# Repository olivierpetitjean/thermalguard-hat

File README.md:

# ThermalGuard HAT

ThermalGuard HAT is a Raspberry Pi HAT for monitoring and controlling airflow in a server rack or enclosed equipment bay.

This repository contains both the hardware design and the software stack:

- a custom KiCad HAT
- a Python hardware service running on the Raspberry Pi
- a .NET 8 API
- an Angular web dashboard

## Demo

https://github.com/user-attachments/assets/547ba5f1-9dda-4290-b39c-db074ba426f6

## Board Renders And Wiring

### KiCad 3D render - front

### KiCad 3D render - back

### Wiring overview

## Features

- System monitoring for onboard temperature, power consumption and relative humidity
- Two configurable temperature probes for rack, ambient or custom placement
- Dual fan control with RPM tracking and airflow estimation
- Onboard display showing temperatures, fan RPM, IP address and MAC address
- Automatic fan curves with linked or independent behavior
- Temporary boost mode to force maximum cooling for a defined duration
- Audible alert when a fan or temperature probe is disconnected
- Onboard button control to mute or disable the audible alert
- Web dashboard with live status cards and historical charts
- History browsing by custom period, day or hour
- Local or remote access with authentication
- Kiosk mode for dedicated wall display or rack display usage
- End-to-end installation assistant, including kiosk setup
- Configurable SQLite storage location, including external USB or disk-based storage

The reference platform for this project is a Raspberry Pi 2B. The goal is also to make practical use of older Raspberry Pi hardware for a dedicated monitoring appliance, rather than requiring a newer and more expensive board.

## Repository Structure

```text
thermalguard-hat/
|-- backend/
|   |-- src/      .NET 8 API, persistence, workers, static frontend hosting
|   `-- tests/    .NET test project
|-- frontend/     Angular frontend
|-- services/     Raspberry Pi hardware service and Python tests
|-- kicad/        KiCad project for the HAT PCB
|-- config/       Shared example configuration
|-- docs/         README media assets
`-- install.sh    Raspberry Pi installation script
```

## Hardware

Main hardware blocks currently present in the project:

- Raspberry Pi 2B host
- custom HAT PCB designed in KiCad
- 2 x DS18B20 probes
- 1 x SHT31D temperature and humidity sensor
- 2 x PWM-controlled fans
- fan tachometer and current measurement circuitry
- OLED display and onboard controls

The repository is not only a software project. It also includes the PCB design files required to fabricate the HAT.

## Software Architecture

```mermaid
flowchart TB
    browser([Browser])
    kiosk([Kiosk Display])
    front["Angular Dashboard"]
    api[".NET 8 API"]
    proxy["MQTT Proxy (/mqtt)"]
    mqtt[("Mosquitto Broker")]
    py["Python Hardware Service"]
    db[("SQLite Database")]
    hw["Sensors / Fans / GPIO"]
    svc["systemd"]

    browser -->|"UI"| front
    kiosk -->|"Kiosk UI"| front
    front -->|"REST"| api
    front -->|"WebSocket MQTT"| proxy
    proxy -->|"MQTT"| mqtt
    mqtt -->|"Live telemetry"| proxy
    py -->|"Publish"| mqtt
    py -->|"Store samples"| db
    api -->|"Read / write"| db
    api -->|"Control service"| svc
    svc -->|"Manage"| py
    py -->|"Read / drive"| hw

    classDef client fill:#202534,stroke:#90a4ff,color:#ffffff,stroke-width:1.5px;
    classDef ui fill:#2f3d56,stroke:#6ea8fe,color:#ffffff,stroke-width:1.5px;
    classDef backend fill:#304b46,stroke:#58c4a3,color:#ffffff,stroke-width:1.5px;
    classDef msg fill:#4b3561,stroke:#d08bff,color:#ffffff,stroke-width:1.5px;
    classDef data fill:#5a4330,stroke:#f2a65a,color:#ffffff,stroke-width:1.5px;
    classDef device fill:#4a3f46,stroke:#ff7b7b,color:#ffffff,stroke-width:1.5px;

    class browser,kiosk client;
    class front ui;
    class api,proxy,svc backend;
    class mqtt msg;
    class db data;
    class py,hw device;
```

### Python service

The Python service is the hardware-facing part of the system. It:

- initializes GPIO and sensors
- controls the fans
- reads live measurements
- publishes telemetry on MQTT
- persists data into SQLite

Main entry points:

- [services/main.py](services/main.py)
- [services/service.py](services/service.py)

### Backend API

The backend is a .NET 8 application that:

- serves the web application
- exposes authenticated API endpoints
- stores and queries historical data
- exposes configuration for the frontend
- manages service status operations

Main entry points:

- [backend/src/NetApi/Program.cs](backend/src/NetApi/Program.cs)
- [backend/src/NetApi/Api/Controllers](backend/src/NetApi/Api/Controllers)

### Frontend

The frontend is an Angular application providing:

- dashboard views
- setup and login screens
- kiosk mode
- live MQTT-backed monitoring cards and graphs

Main entry points:

- [frontend/src/app/features/dashboard/pages/dashboard.component.ts](frontend/src/app/features/dashboard/pages/dashboard.component.ts)
- [frontend/src/app/core/app.routes.ts](frontend/src/app/core/app.routes.ts)

## Dashboard

The web interface provides both live monitoring cards and historical charts.

### Live overview

### History view

## Kiosk Mode

ThermalGuard HAT can run in kiosk mode for a dedicated rack display, with optional autologin, Chromium autostart, cursor hiding and screen blanking control.

https://github.com/user-attachments/assets/b98a219e-978e-4593-a772-88bbc4d270f7

## Installation

Run the installation script on the Raspberry Pi as root:

```bash
sudo bash -c "$(curl -sSL https://raw.githubusercontent.com/olivierpetitjean/thermalguard-hat/main/install.sh)"
```

The script installs the software stack, prepares the Raspberry Pi environment and deploys the backend, frontend and Python service.

## Storage Recommendation

For a permanent installation, it is strongly recommended to store the SQLite database on an external storage device such as:

- a USB flash drive
- an external SSD
- an external hard drive

Reason:

- the system performs repeated read and write operations
- keeping the database on the Raspberry Pi SD card increases wear
- the SD card also hosts the operating system, so avoiding unnecessary writes improves reliability

The database location is configurable through the shared connection string in [config/settings.example.json](config/settings.example.json).

## Configuration

The main configuration reference is [config/settings.example.json](config/settings.example.json).

The setup wizard intentionally hides a few advanced low-level values such as the GPIO chip index and PWM channel mapping. They remain available in the shared configuration file if manual tuning is ever needed.

The installation also runs an interactive configuration wizard. Its main sections are:

| Wizard section | What it configures |
|---|---|
| `API & Security` | CORS origin, JWT secret, token lifetime, retention policy and kiosk IP bypass rules |
| `Display & Naming` | Dashboard title, sensor names, fan names, locale, units and airflow display values |
| `Kiosk Mode` | Dedicated kiosk display behavior, local user, inline layout, cursor hiding, autologin, screen blanking and autostart |
| `MQTT Broker` | Local Mosquitto setup, WebSocket port, optional local authentication and optional MQTT bridge settings |
| `1-Wire Temperature Sensors` | Detection and assignment of the two DS18B20 probe identifiers |
| `Thresholds & Timing` | System fan threshold, database write interval, LCD screen standby delay, fan tach filter and PWM timing settings |

If kiosk mode is enabled, the installer then runs a second kiosk-specific step to apply the desktop autologin, screen blanking and Chromium autostart configuration.

### Core settings

| Key | Purpose | Example |
|---|---|---|
| `ConnectionStrings.WebApiDatabase` | Shared SQLite database path used by the API and Python service | `Data Source=/opt/thermalguard-hat/api/db/LocalDatabase.db` |
| `RetentionDays` | Number of days of historical data to keep | `30` |
| `Auth.JwtSecret` | Secret used to sign JWT tokens | `change-me-in-production-at-least-32-chars!!` |
| `Auth.TokenExpiryHours` | JWT validity duration in hours | `12` |
| `AllowedOrigins` | Allowed frontend origin for CORS | `http://raspberrypi.local` |

### MQTT and broker settings

| Key | Purpose | Example |
|---|---|---|
| `BrokerHostSettings.Host` | MQTT broker hostname or IP | `127.0.0.1` |
| `BrokerHostSettings.Port` | MQTT TCP port | `1883` |
| `BrokerHostSettings.WsPort` | MQTT over WebSocket port | `1884` |
| `BrokerHostSettings.User` | MQTT username | `your-user` |
| `BrokerHostSettings.Password` | MQTT password | `your-password` |
| `BrokerHostSettings.UseTls` | Enable TLS for broker communication | `false` |
| `Mosquitto.Local.Authentication.Enabled` | Enable authentication on local Mosquitto | `false` |
| `Mosquitto.Bridge.Enabled` | Enable broker bridge mode | `false` |
| `Mosquitto.Bridge.Host` | Upstream broker hostname | `mqtt.example.com` |
| `Mosquitto.Bridge.Port` | Upstream broker port | `1883` |

### Sensors, cooling and hardware pins

| Key | Purpose | Example |
|---|---|---|
| `Python.Sensor1Uid` | 1-Wire identifier for probe 1 | `xxxxxxxxxxxx` |
| `Python.Sensor2Uid` | 1-Wire identifier for probe 2 | `xxxxxxxxxxxx` |
| `Python.SysFanThreshold` | Temperature threshold for the system fan | `38` |
| `Python.Fan1Pin` | PWM pin for fan 1 | `12` |
| `Python.Fan2Pin` | PWM pin for fan 2 | `13` |
| `Python.Fan1Sensor` | Tachometer input for fan 1 | `25` |
| `Python.Fan2Sensor` | Tachometer input for fan 2 | `24` |
| `Python.SystemFan` | GPIO pin for the auxiliary system fan | `23` |
| `Python.SysBuzzer` | GPIO pin for the buzzer | `22` |
| `Python.Button1Pin` | GPIO pin for button 1 | `17` |
| `Python.Button2Pin` | GPIO pin for button 2 | `0` |

### Display and UI labels

| Key | Purpose | Example |
|---|---|---|
| `Display.DashboardTitle` | Dashboard title shown in the UI | `Dashboard` |
| `Display.Sensor1Name` | Label for probe 1 | `Rack` |
| `Display.Sensor2Name` | Label for probe 2 | `Ambient` |
| `Display.Fan1Name` | Label for fan 1 | `Intake Fan` |
| `Display.Fan2Name` | Label for fan 2 | `Exhaust Fan` |
| `Display.Locale` | UI locale | `en-US` |
| `Display.TemperatureUnit` | Temperature unit | `C` |
| `Display.AirflowUnit` | Airflow unit displayed in the UI | `m3h` |
| `Display.Fan1MaxAirflow` | Reference airflow value for fan 1 | `95.0` |
| `Display.Fan2MaxAirflow` | Reference airflow value for fan 2 | `95.0` |

### Kiosk settings

| Key | Purpose | Example |
|---|---|---|
| `Kiosk.BypassIPs` | IP addresses allowed to access kiosk mode without standard login | `[]` |
| `KioskSetup.Enabled` | Enable kiosk setup during installation | `false` |
| `KioskSetup.User` | Desktop user used for kiosk autologin | `pi` |
| `KioskSetup.HideCursor` | Hide mouse cursor in kiosk mode | `true` |
| `KioskSetup.DesktopAutologin` | Enable desktop autologin | `true` |
| `KioskSetup.DisableScreenBlanking` | Disable screen blanking and sleep | `true` |
| `KioskSetup.Autostart` | Launch kiosk automatically on boot | `true` |

## Security

- API endpoints are protected with JWT authentication except the authentication bootstrap endpoints
- passwords are hashed with BCrypt
- the JWT secret must be changed before deployment
- CORS origins should be restricted to the actual deployed frontend origin

## License

MIT. See [LICENSE](LICENSE).

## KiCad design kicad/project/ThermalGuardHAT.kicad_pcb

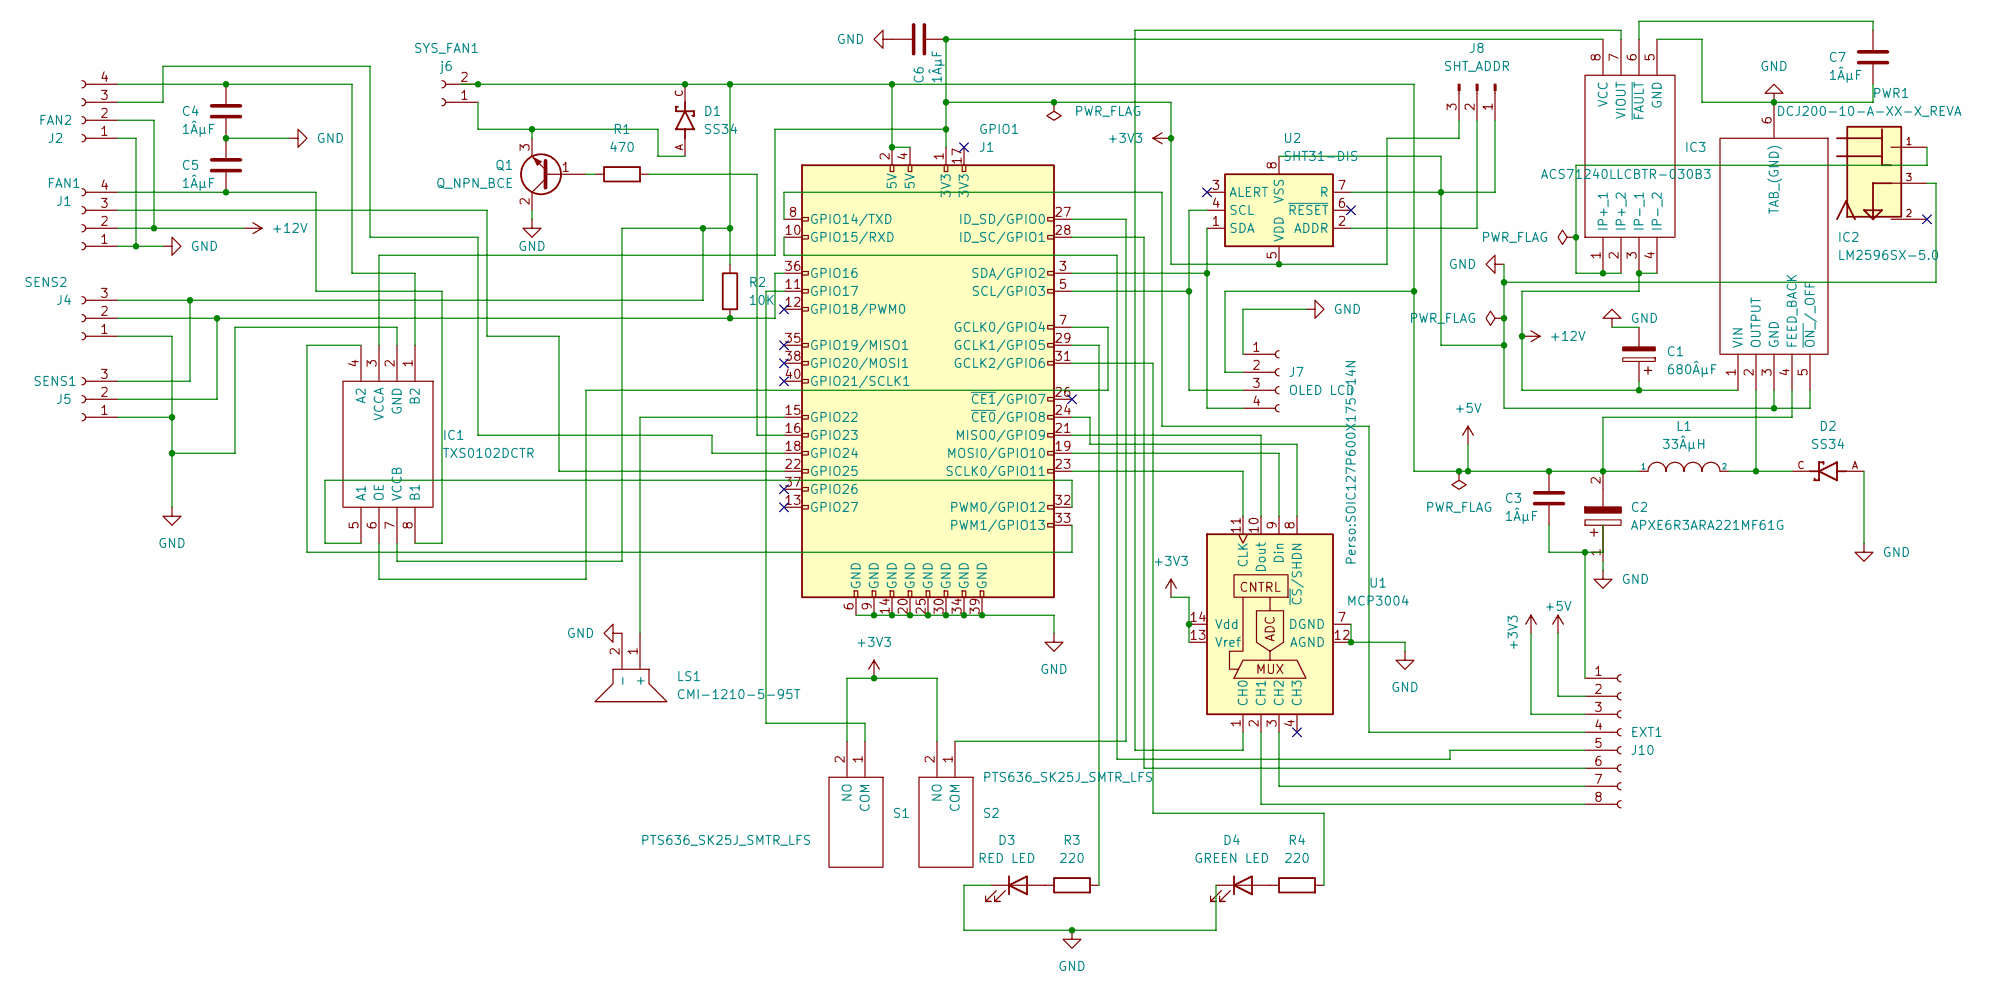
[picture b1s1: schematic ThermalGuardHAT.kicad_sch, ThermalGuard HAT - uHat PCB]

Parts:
C1: 680ÂµF; CAPAE1030X1270N
C2: APXE6R3ARA221MF61G; CAPAE1030X1270N; Mouser Part Number 661-APXE6R3A221MF61G
C3, C4, C5, C6, C7: 1ÂµF; C_0805_2012Metric
D1, D2: SS34; DIOM4325X250N; PARTREV 31 Aug 2016
D3: RED LED; LED_0603_1608Metric
D4: GREEN LED; LED_0603_1608Metric
EXT1: J10; PinHeader_1x08_P2.54mm_Vertical
FAN1: J1; FanPinHeader_1x04_P2.54mm_Vertical
FAN2: J2; FanPinHeader_1x04_P2.54mm_Vertical
GPIO1: J1; PinHeader_2x20_P2.54mm_Vertical
IC1: TXS0102DCTR; SOP65P400X130-8N; Mouser Part Number 595-TXS0102DCTR
IC2: LM2596SX-5.0; TO-263-5_TabPin6; Mouser Part Number 926-LM2596SX-5.0NOPB
IC3: ACS71240LLCBTR-030B3; SOIC127P600X175-8N; Mouser Part Number 250-71240LLCBTR030B3
J7: OLED LCD; PinHeader_1x04_P2.54mm_Vertical
J8: SHT_ADDR; PinHeader_1x03_P2.54mm_Vertical
L1: 33ÂµH; SRR1280-331K
LS1: CMI-1210-5-95T; CMI1210595T; Mouser Part Number 179-CMI-1210-5-95T
PWR1: DCJ200-10-A-XX-X_REVA; BarrelJack_CLIFF_FC681465S_SMT_Horizontal
Q1: Q_NPN_BCE; SOT-23
R1: 470; R_0805_2012Metric
R2: 10K; R_0805_2012Metric
R3, R4: 220; R_0805_2012Metric
S1, S2: PTS636_SK25J_SMTR_LFS; PTS636SK25JSMTRLFS; Mouser Part Number 611-PTS636SK25JSMTRL
SENS1: J5; FanPinHeader_1x03_P2.54mm_Vertical
SENS2: J4; FanPinHeader_1x03_P2.54mm_Vertical
SYS_FAN1: j6; JST_XH_B2B-XH-A_1x02_P2.50mm_Vertical
U1: MCP3004; SOIC127P600X175-14N
U2: SHT31-DIS; Sensirion_DFN-8-1EP_2.5x2.5mm_P0.5mm_EP1.1x1.7mm

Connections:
+3V3: C6.2, EXT1.3, GPIO1.1 (3V3), IC1.3 (VCCA), IC3.8 (VCC), J8.3, S1.2 (NO), S2.2 (NO), U1.13 (Vref), U1.14 (Vdd), U2.5 (VDD)
+5V: C2.2, C3.1, D1.C, EXT1.2, GPIO1.2 (5V), GPIO1.4 (5V), IC1.7 (VCCB), IC2.4 (FEED_BACK), J7.2, L1.1, R2.1, SENS1.3, SENS2.3, SYS_FAN1.2
+12V: C1.1, FAN1.2, FAN2.2, IC2.1 (VIN), IC3.3 (IP-_1), IC3.4 (IP-_2)
GND: C1.2, C2.1, C4.2, C5.1, C6.1, C7.2, D2.A, D3.1 (K), D4.1 (K), FAN1.1, FAN2.1, GPIO1.6 (GND), GPIO1.9 (GND), GPIO1.14 (GND), GPIO1.20 (GND), GPIO1.25 (GND), GPIO1.30 (GND), GPIO1.34 (GND), GPIO1.39 (GND), IC1.2 (GND), IC2.3 (GND), IC2.5 (~ON_/_OFF), IC2.6 (TAB_(GND)), IC3.5 (GND), J7.1, J8.1, LS1.2 (-), PWR1.3, Q1.2 (C), SENS1.1, SENS2.1, U1.7 (DGND), U1.12 (AGND), U2.7 (R), U2.8 (VSS), U2.9 (VSS)
unnamed: C3.2, EXT1.1
unnamed: C4.1, FAN2.4, IC1.1 (B2)
unnamed: C5.2, FAN1.4, IC1.8 (B1)
unnamed: C7.1, IC3.6 (~FAULT)
unnamed: D1.A, Q1.3 (E), SYS_FAN1.1
unnamed: D2.C, IC2.2 (OUTPUT), L1.2
unnamed: D3.2 (A), R3.1
unnamed: D4.2 (A), R4.1
unnamed: EXT1.4, GPIO1.8 (GPIO14/TXD)
unnamed: EXT1.5, GPIO1.10 (GPIO15/RXD)
unnamed: EXT1.6, GPIO1.28 (ID_SC/GPIO1)
unnamed: EXT1.7, U1.3 (CH2)
unnamed: EXT1.8, U1.2 (CH1)
unnamed: FAN1.3, GPIO1.22 (GPIO25)
unnamed: FAN2.3, GPIO1.18 (GPIO24)
unnamed: GPIO1.3 (SDA/GPIO2), J7.4, U2.1 (SDA)
unnamed: GPIO1.5 (SCL/GPIO3), J7.3, U2.4 (SCL)
unnamed: GPIO1.7 (GCLK0/GPIO4), IC1.6 (OE)
unnamed: GPIO1.11 (GPIO17), S1.1 (COM)
unnamed: GPIO1.15 (GPIO22), LS1.1 (+)
unnamed: GPIO1.16 (GPIO23), R1.2
unnamed: GPIO1.19 (MOSI0/GPIO10), U1.9 (Din)
unnamed: GPIO1.21 (MISO0/GPIO9), U1.10 (Dout)
unnamed: GPIO1.23 (SCLK0/GPIO11), U1.11 (CLK)
unnamed: GPIO1.24 (~CE0/GPIO8), U1.8 (~CS/SHDN)
unnamed: GPIO1.27 (ID_SD/GPIO0), S2.1 (COM)
unnamed: GPIO1.29 (GCLK1/GPIO5), R3.2
unnamed: GPIO1.31 (GCLK2/GPIO6), R4.2
unnamed: GPIO1.32 (PWM0/GPIO12), IC1.5 (A1)
unnamed: GPIO1.33 (PWM1/GPIO13), IC1.4 (A2)
unnamed: GPIO1.36 (GPIO16), R2.2, SENS1.2, SENS2.2
unnamed: IC3.1 (IP+_1), IC3.2 (IP+_2), PWR1.1
unnamed: IC3.7 (VIOUT), U1.1 (CH0)
unnamed: J8.2, U2.2 (ADDR)
unnamed: Q1.1 (B), R1.1

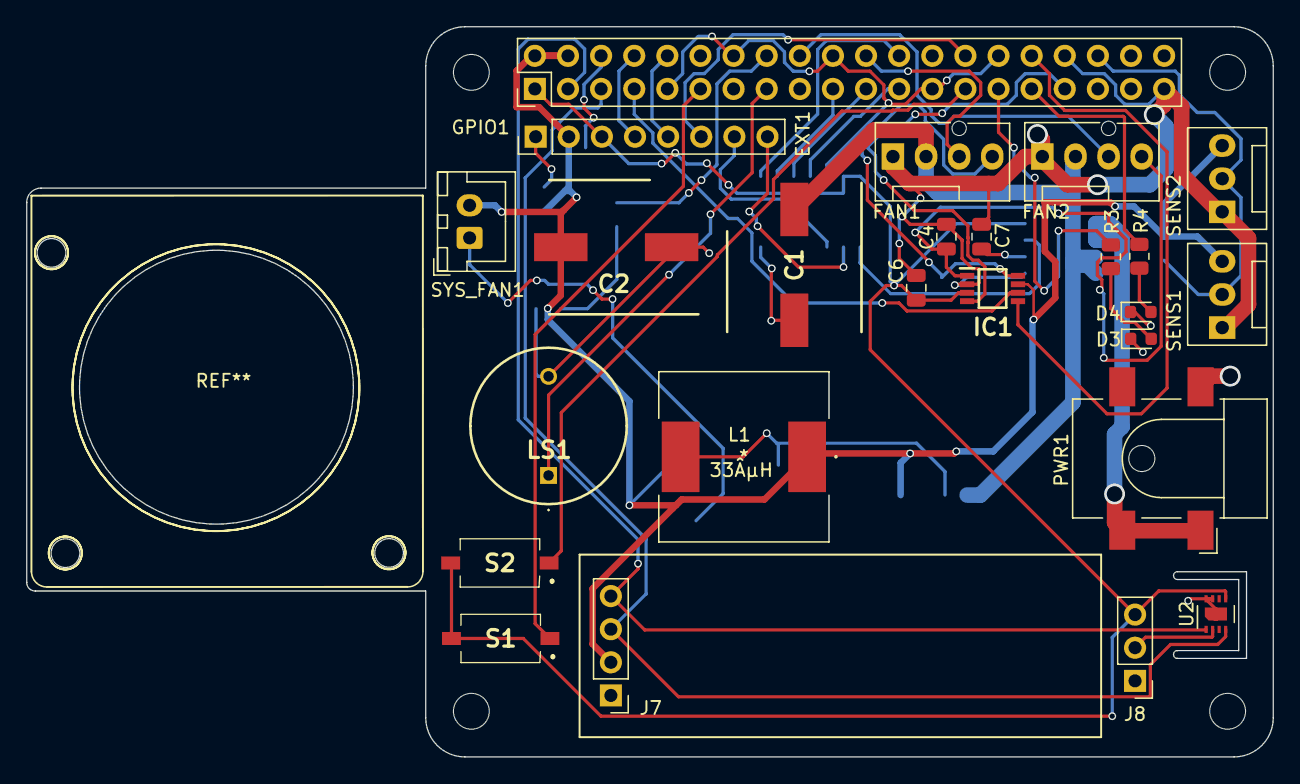
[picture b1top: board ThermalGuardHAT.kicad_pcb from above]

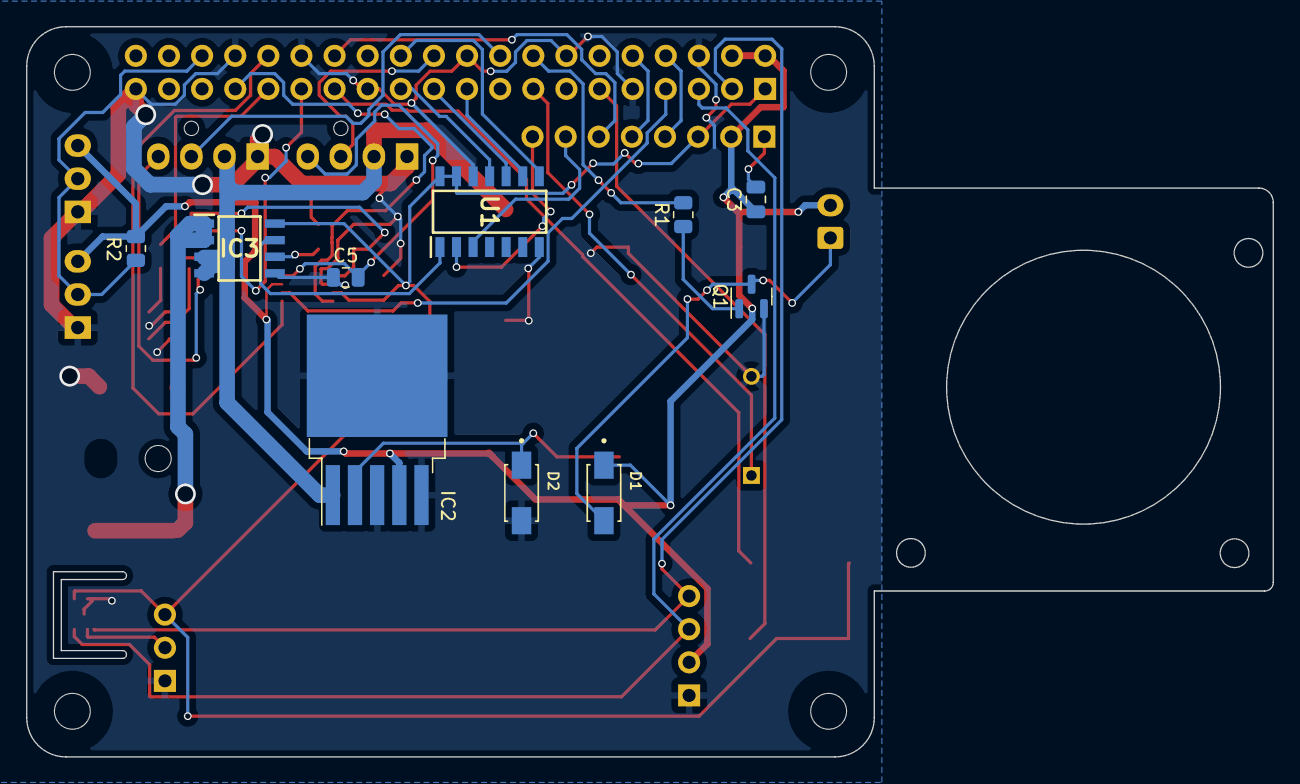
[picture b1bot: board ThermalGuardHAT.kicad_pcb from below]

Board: 2 copper layers, 95.6 x 56.0 mm, 35 parts (10 on the bottom side), 39 nets.

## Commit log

2026-04-13 docs(readme): update demo video links
2026-04-23 Add multi-mode fan condition control
2026-05-20 Add fan alert toggle and installation changelog

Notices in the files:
parts and their libraries:
Copyright 2021 Accelerated Designs. All rights reserved.
